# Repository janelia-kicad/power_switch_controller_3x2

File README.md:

- [Repository Information](#orge525b0b)
  - [Description](#org0bc1c6c)
- [Images](#org26ba3c3)
- [Schematic](#org31a6ed4)
- [Gerbers](#org7ba7e0c)
- [Bill of Materials](#orga80dabd)
  - [PCB Parts](#orgc05bb46)
  - [Supplemental Parts](#org1c6e48d)
  - [Vendor Parts Lists](#org0d3d511)
- [Supplemental Documentation](#org3926df8)
  - [Assembly Instructions](#org50c1561)

# Repository Information

-   **Name:** power\_switch\_controller\_3x2
-   **Version:** 1.1
-   **License:** Open-Source Hardware
-   **URL:** <https://github.com/janelia-kicad/power_switch_controller_3x2>
-   **Author:** Peter Polidoro
-   **Email:** peter@polidoro.io

## Description

This board controls up to 8 low-side power switches for turning on and off solenoids, relays, and resistive loads.

# Images

# Schematic

[./schematic/power\_switch\_controller\_3x2.pdf](./schematic/power_switch_controller_3x2.pdf)

# Gerbers

Send gerbers zip file to your favorite PCB manufacturer for fabrication.

[./gerbers/power\_switch\_controller\_5x3\_v1.1.zip](./gerbers/power_switch_controller_5x3_v1.1.zip)

# Bill of Materials

## PCB Parts

| Item | Reference(s)               | Quantity | PartNumber     | Vendor  | Description                               |
|---- |-------------------------- |-------- |-------------- |------- |----------------------------------------- |
| 1    | C1                         | 1        | 445-4536-1-ND  | digikey | CAP CER 10UF 50V 10% X7S 1210             |
| 2    | C2                         | 1        | 399-13229-1-ND | digikey | CAP CER 0.1UF 100V X7R 1210               |
| 3    | D1                         | 1        | 568-11697-1-ND | digikey | DIODE SCHOTTKY 45V 10A CFP15              |
| 4    | D2 D3 D4 D5 D6 D7 D8 D9    | 8        | CMHD3595 CT-ND | digikey | DIODE GEN PURP 150V 150MA SOD123          |
| 5    | L1 L2 L3 L4 L5 L6 L7 L8 L9 | 9        | 350-1723-ND    | digikey | LED 2MM 24V VERTICAL RED PC MNT           |
| 6    | MDB1                       | 2        | S1011E-16-ND   | digikey | 16 Position Header Through Hole Male Pins |
| 7    | P1                         | 1        | CP-063BH-ND    | digikey | CONN PWR JACK DC 2.5X5.5 8A T/H           |
| 8    | P2                         | 1        | S9187-ND       | digikey | CONN HEADR 2.54MM 16POS GOLD SMD          |
| 9    | SW1                        | 1        | 360-2610-ND    | digikey | SWITCH SLIDE SPST 0.4VA 28V               |
| 10   | U1                         | 1        | TLE7230RCT-ND  | digikey | IC SW SMART OCTAL LOWSIDE PDSO36          |

## Supplemental Parts

| Item | Quantity | PartNumber   | Vendor  | Description                       |
|---- |-------- |------------ |------- |--------------------------------- |
| 1    | 32       | WM2800-ND    | digikey | CONN HOUSING 2POS .100 SINGLE     |
| 2    | 64       | WM2512-ND    | digikey | CONN TERM FEMALE 22-24AWG GOLD    |
| 3    | 64       | WM2513-ND    | digikey | CONN TERM FEMALE 24-30AWG GOLD    |
| 4    | 4        | AKC16H-ND    | digikey | CONN IDC SKT 16POS W/POL 15 GOLD  |
| 5    | 1        | MC16M-300-ND | digikey | CBL RIBN 16COND 0.050 MULTI 300ft |
| 6    | 4        | APK16B-ND    | digikey | CONN IDC PIN 16POS 30AU NO LATCH  |
| 7    | 32       | WM2900-ND    | digikey | CONN HOUSING 2POS .100 W/LATCH    |
| 8    | 64       | WM2570-ND    | digikey | CONN TERM FEMALE 22-24AWG GOLD    |
| 9    | 64       | WM2572-ND    | digikey | CONN SOCKET 24-30AWG CRIMP 30AU   |
| 10   | 32       | WM2533-ND    | digikey | CONN HOUSING MALE 2POS .100       |
| 11   | 64       | WM2566-ND    | digikey | CONN PIN 24-30AWG CRIMP 30GOLD    |
| 12   | 64       | WM2567-ND    | digikey | CONN TERM MALE 22-24AWG GOLD      |

## Vendor Parts Lists

[./bom/digikey\_parts.csv](./bom/digikey_parts.csv)

[./bom/supplemental\_digikey\_parts.csv](./bom/supplemental_digikey_parts.csv)

# Supplemental Documentation

## Assembly Instructions

-   Solder header pins into the driver board, making note of TOP label. Insert header pins on bottom of board so that the long unsoldered header pins point down when the TOP label faces up.
-   Solder surface mount and through hole components onto the pcb.

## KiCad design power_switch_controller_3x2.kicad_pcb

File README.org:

# Created 2018-07-11 Wed 14:41
#+OPTIONS: title:nil author:nil email:nil toc:t |:t ^:nil
* Repository Information

- Name :: power_switch_controller_3x2
- Version :: 1.1
- License :: Open-Source Hardware
- URL :: https://github.com/janelia-kicad/power_switch_controller_3x2
- Author :: Peter Polidoro
- Email :: peter@polidoro.io

** Description

This board controls up to 8 low-side power switches for turning on and off
solenoids, relays, and resistive loads.

* Images

[[file:./images/top.png]]

[[file:./images/bottom.png]]

* Schematic

[[file:./schematic/power_switch_controller_3x2.pdf][./schematic/power_switch_controller_3x2.pdf]]

[[file:./schematic/images/schematic00.png]]

[[file:./schematic/images/schematic01.png]]

* Gerbers

Send gerbers zip file to your favorite PCB manufacturer for fabrication.

[[file:./gerbers/power_switch_controller_5x3_v1.1.zip][./gerbers/power_switch_controller_5x3_v1.1.zip]]

[[file:./gerbers/images/gerbers00.png]]

[[file:./gerbers/images/gerbers01.png]]

* Bill of Materials

** PCB Parts

| Item | Reference(s)               | Quantity | PartNumber     | Vendor  | Description                               |
|------+----------------------------+----------+----------------+---------+-------------------------------------------|
|    1 | C1                         |        1 | 445-4536-1-ND  | digikey | CAP CER 10UF 50V 10% X7S 1210             |
|    2 | C2                         |        1 | 399-13229-1-ND | digikey | CAP CER 0.1UF 100V X7R 1210               |
|    3 | D1                         |        1 | 568-11697-1-ND | digikey | DIODE SCHOTTKY 45V 10A CFP15              |
|    4 | D2 D3 D4 D5 D6 D7 D8 D9    |        8 | CMHD3595 CT-ND | digikey | DIODE GEN PURP 150V 150MA SOD123          |
|    5 | L1 L2 L3 L4 L5 L6 L7 L8 L9 |        9 | 350-1723-ND    | digikey | LED 2MM 24V VERTICAL RED PC MNT           |
|    6 | MDB1                       |        2 | S1011E-16-ND   | digikey | 16 Position Header Through Hole Male Pins |
|    7 | P1                         |        1 | CP-063BH-ND    | digikey | CONN PWR JACK DC 2.5X5.5 8A T/H           |
|    8 | P2                         |        1 | S9187-ND       | digikey | CONN HEADR 2.54MM 16POS GOLD SMD          |
|    9 | SW1                        |        1 | 360-2610-ND    | digikey | SWITCH SLIDE SPST 0.4VA 28V               |
|   10 | U1                         |        1 | TLE7230RCT-ND  | digikey | IC SW SMART OCTAL LOWSIDE PDSO36          |

** Supplemental Parts

| Item | Quantity | PartNumber   | Vendor  | Description                       |
|------+----------+--------------+---------+-----------------------------------|
|    1 |       32 | WM2800-ND    | digikey | CONN HOUSING 2POS .100 SINGLE     |
|    2 |       64 | WM2512-ND    | digikey | CONN TERM FEMALE 22-24AWG GOLD    |
|    3 |       64 | WM2513-ND    | digikey | CONN TERM FEMALE 24-30AWG GOLD    |
|    4 |        4 | AKC16H-ND    | digikey | CONN IDC SKT 16POS W/POL 15 GOLD  |
|    5 |        1 | MC16M-300-ND | digikey | CBL RIBN 16COND 0.050 MULTI 300ft |
|    6 |        4 | APK16B-ND    | digikey | CONN IDC PIN 16POS 30AU NO LATCH  |
|    7 |       32 | WM2900-ND    | digikey | CONN HOUSING 2POS .100 W/LATCH    |
|    8 |       64 | WM2570-ND    | digikey | CONN TERM FEMALE 22-24AWG GOLD    |
|    9 |       64 | WM2572-ND    | digikey | CONN SOCKET 24-30AWG CRIMP 30AU   |
|   10 |       32 | WM2533-ND    | digikey | CONN HOUSING MALE 2POS .100       |
|   11 |       64 | WM2566-ND    | digikey | CONN PIN 24-30AWG CRIMP 30GOLD    |
|   12 |       64 | WM2567-ND    | digikey | CONN TERM MALE 22-24AWG GOLD      |

** Vendor Parts Lists

[[file:./bom/digikey_parts.csv][./bom/digikey_parts.csv]]

[[file:./bom/supplemental_digikey_parts.csv][./bom/supplemental_digikey_parts.csv]]

* Supplemental Documentation

** Assembly Instructions

- Solder header pins into the driver board, making note of TOP label.
  Insert header pins on bottom of board so that the long unsoldered header
  pins point down when the TOP label faces up.
- Solder surface mount and through hole components onto the pcb.

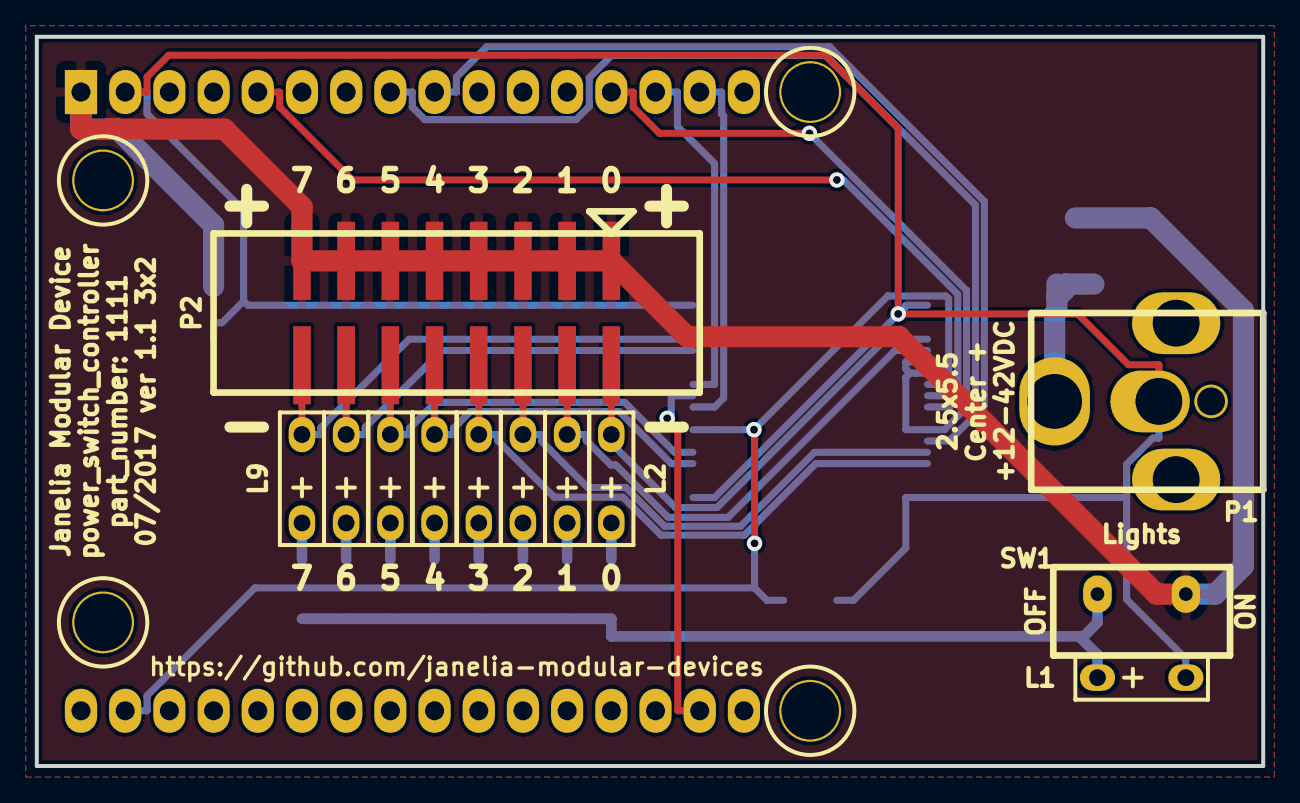
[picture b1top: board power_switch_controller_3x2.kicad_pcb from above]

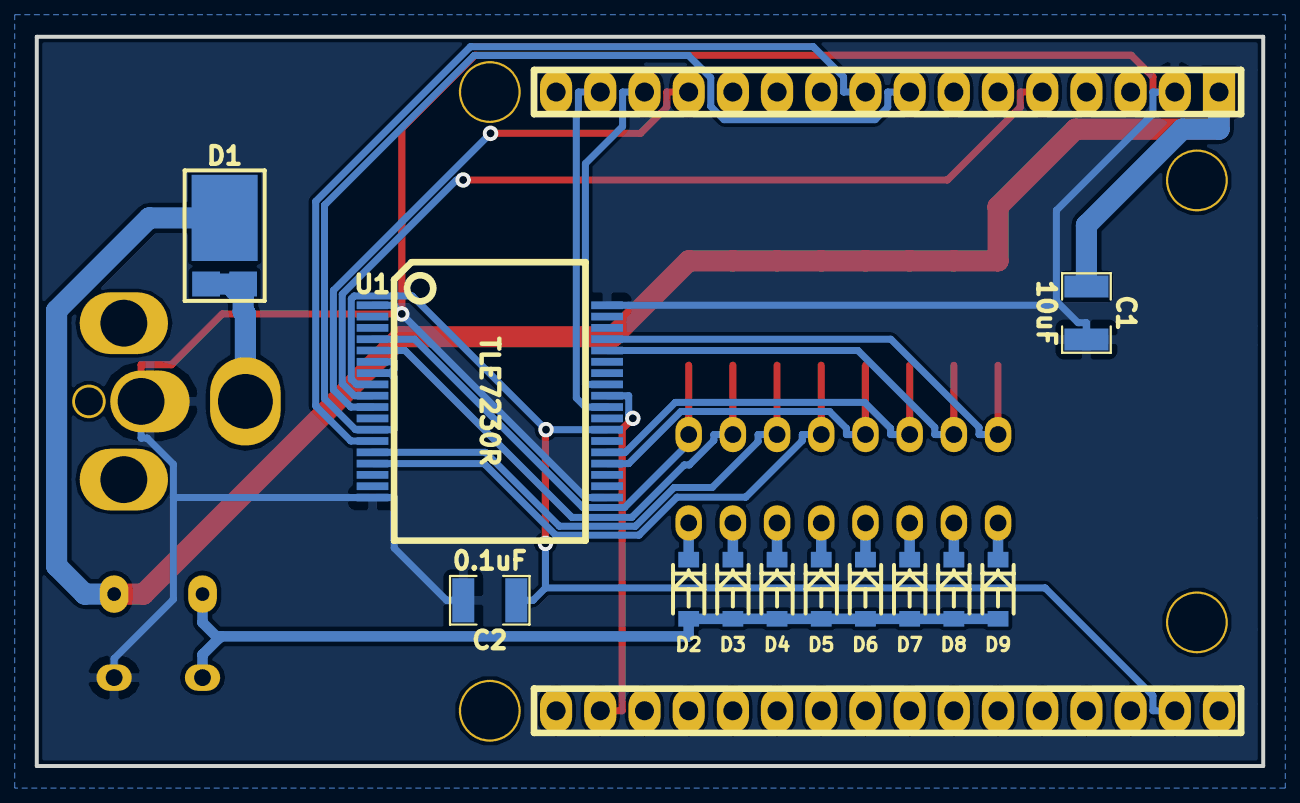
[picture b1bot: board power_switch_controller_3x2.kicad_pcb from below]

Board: 2 copper layers, 70.5 x 41.9 mm, 25 parts (12 on the bottom side), 28 nets.

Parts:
C1: 10uF; SM1210
C2: 0.1uF; SM1210
D1: diode_schottky_45V_10A; CFP15
D2, D3, D4, D5, D6, D7, D8, D9: diode_low_rev_current; SOD-123
L1, L2, L3, L4, L5, L6, L7, L8, L9: LED_24V; LED_555-3XXX
MDB1: MODULAR_DEVICE_BASE_3X2_MALE
P1: PWR_JACK_2.5x5.5; DCJACK_2PIN_HIGHCURRENT
P2: HEADER_02X08_SMD; HEADER_02x08_SMD
SW1: SPST_SLIDE_AS
U1: TLE7230R; PG-DSO-36

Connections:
/CS: MDB1.10, U1.10
/IN: MDB1.5, U1.6, U1.7, U1.12
/MAP: MDB1.6, U1.13
/MISO: MDB1.12, U1.27
/MOSI: MDB1.11, U1.29
/RESET: MDB1.2, U1.9
/SCK: MDB1.13, U1.28
/channels_0-7/LP_0: D2.1, L2.1
/channels_0-7/LP_1: D3.1, L3.1
/channels_0-7/LP_2: D4.1, L4.1
/channels_0-7/LP_3: D5.1, L5.1
/channels_0-7/LP_4: D6.1, L6.1
/channels_0-7/LP_5: D7.1, L7.1
/channels_0-7/LP_6: D8.1, L8.1
/channels_0-7/LP_7: D9.1, L9.1
/channels_0-7/OUT_0: L2.2, P2.2, U1.4
/channels_0-7/OUT_1: L3.2, P2.4, U1.5
/channels_0-7/OUT_2: L4.2, P2.6, U1.14
/channels_0-7/OUT_3: L5.2, P2.8, U1.15
/channels_0-7/OUT_4: L6.2, P2.10, U1.22
/channels_0-7/OUT_5: L7.2, P2.12, U1.23
/channels_0-7/OUT_6: L8.2, P2.14, U1.32
/channels_0-7/OUT_7: L9.2, P2.16, U1.33
GND: C1.2, C2.2, L1.2, MDB1.GND, P1.2, U1.1, U1.18, U1.19, U1.36
LED_PWR: D2.2, D3.2, D4.2, D5.2, D6.2, D7.2, D8.2, D9.2, L1.1, SW1.3
VAA: D1.2, P1.1
VDD: C1.1, D1.1, MDB1.VDD, P2.1, P2.3, P2.5, P2.7, P2.9, P2.11, P2.13, P2.15, SW1.1
VEE: C2.1, MDB1.VEE, U1.8, U1.25

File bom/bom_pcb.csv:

Item,Reference(s),Value,Quantity,Description,PartNumber,Vendor
1,C1,10uF,1,CAP CER 10UF 50V 10% X7S 1210,445-4536-1-ND,digikey
2,C2,0.1uF,1,CAP CER 0.1UF 50V 10% X7R 1210,478-3586-1-ND,digikey
3,D1,diode_schottky_45V_10A,1,DIODE SCHOTTKY 45V 10A CFP15,568-11697-1-ND,digikey
4,D2 D3 D4 D5 D6 D7 D8 D9,diode_low_rev_current,8,DIODE GEN PURP 150V 150MA SOD123,CMHD3595 CT-ND,digikey
5,L1 L2 L3 L4 L5 L6 L7 L8 L9,LED_24V,9,LED 2MM 24V VERTICAL RED PC MNT,350-1723-ND,digikey
6,MDB1,MODULAR_DEVICE_BASE_3X2_MALE,2,16 Position Header Through Hole Male Pins,S1011E-16-ND,digikey
7,P1,PWR_JACK_2.5x5.5,1,CONN PWR JACK DC 2.5X5.5 8A T/H,CP-063BH-ND,digikey
8,P2,HEADER_02X08_SMD,1,CONN HEADR 2.54MM 16POS GOLD SMD,S9187-ND,digikey
9,SW1,SPST_SLIDE_AS,1,SWITCH SLIDE SPST 0.4VA 28V,360-2610-ND,digikey
10,U1,TLE7230R,1,IC SW SMART OCTAL LOWSIDE PDSO36,TLE7230RCT-ND,digikey

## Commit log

2017-05-05 Initial commit.
2017-06-06 template -> power_switch_controller.
2017-06-06 Added footprints and components.
2017-06-07 Added power jack and diode.
2017-06-07 Progress towards v1.0.
2017-06-07 Finished v1.0.
2017-06-07 Updated boms.
2017-06-07 Added gerber zip file.
2017-07-14 Removed deprecated cmp file.
2017-07-14 Version 1.1.
2017-09-13 Updated 0.1uF capacitors.
2017-09-22 Removed extra libraries.
2018-01-08 Updated to v4.
2018-01-08 Added v4 files.
2018-01-08 Updated gitignore.
2018-03-09 Update license from software to hardware.
2018-04-12 README.md -> README.org.
2018-04-19 Added .DS_Store to .gitignore.
2018-05-16 Added generate_kicad_documentation submodule.
2018-05-17 Updated submodules.
2018-07-11 Added images.
2018-07-11 Added some supplementals.
2018-07-11 Updated documentation.
2018-07-11 Fixed documentation typo.
2018-08-12 Marked extra Teensy pins.
2018-08-12 Removed v4 files.
2018-08-24 Removed F.SilkS from pads.
2018-08-27 Removed *.SilkS from pads.
2018-11-02 Added README.md.
2021-09-16 Update email address
2021-09-21 Remove ignored files
2022-02-22 Add guix files
2022-02-23 Add guix documentation
